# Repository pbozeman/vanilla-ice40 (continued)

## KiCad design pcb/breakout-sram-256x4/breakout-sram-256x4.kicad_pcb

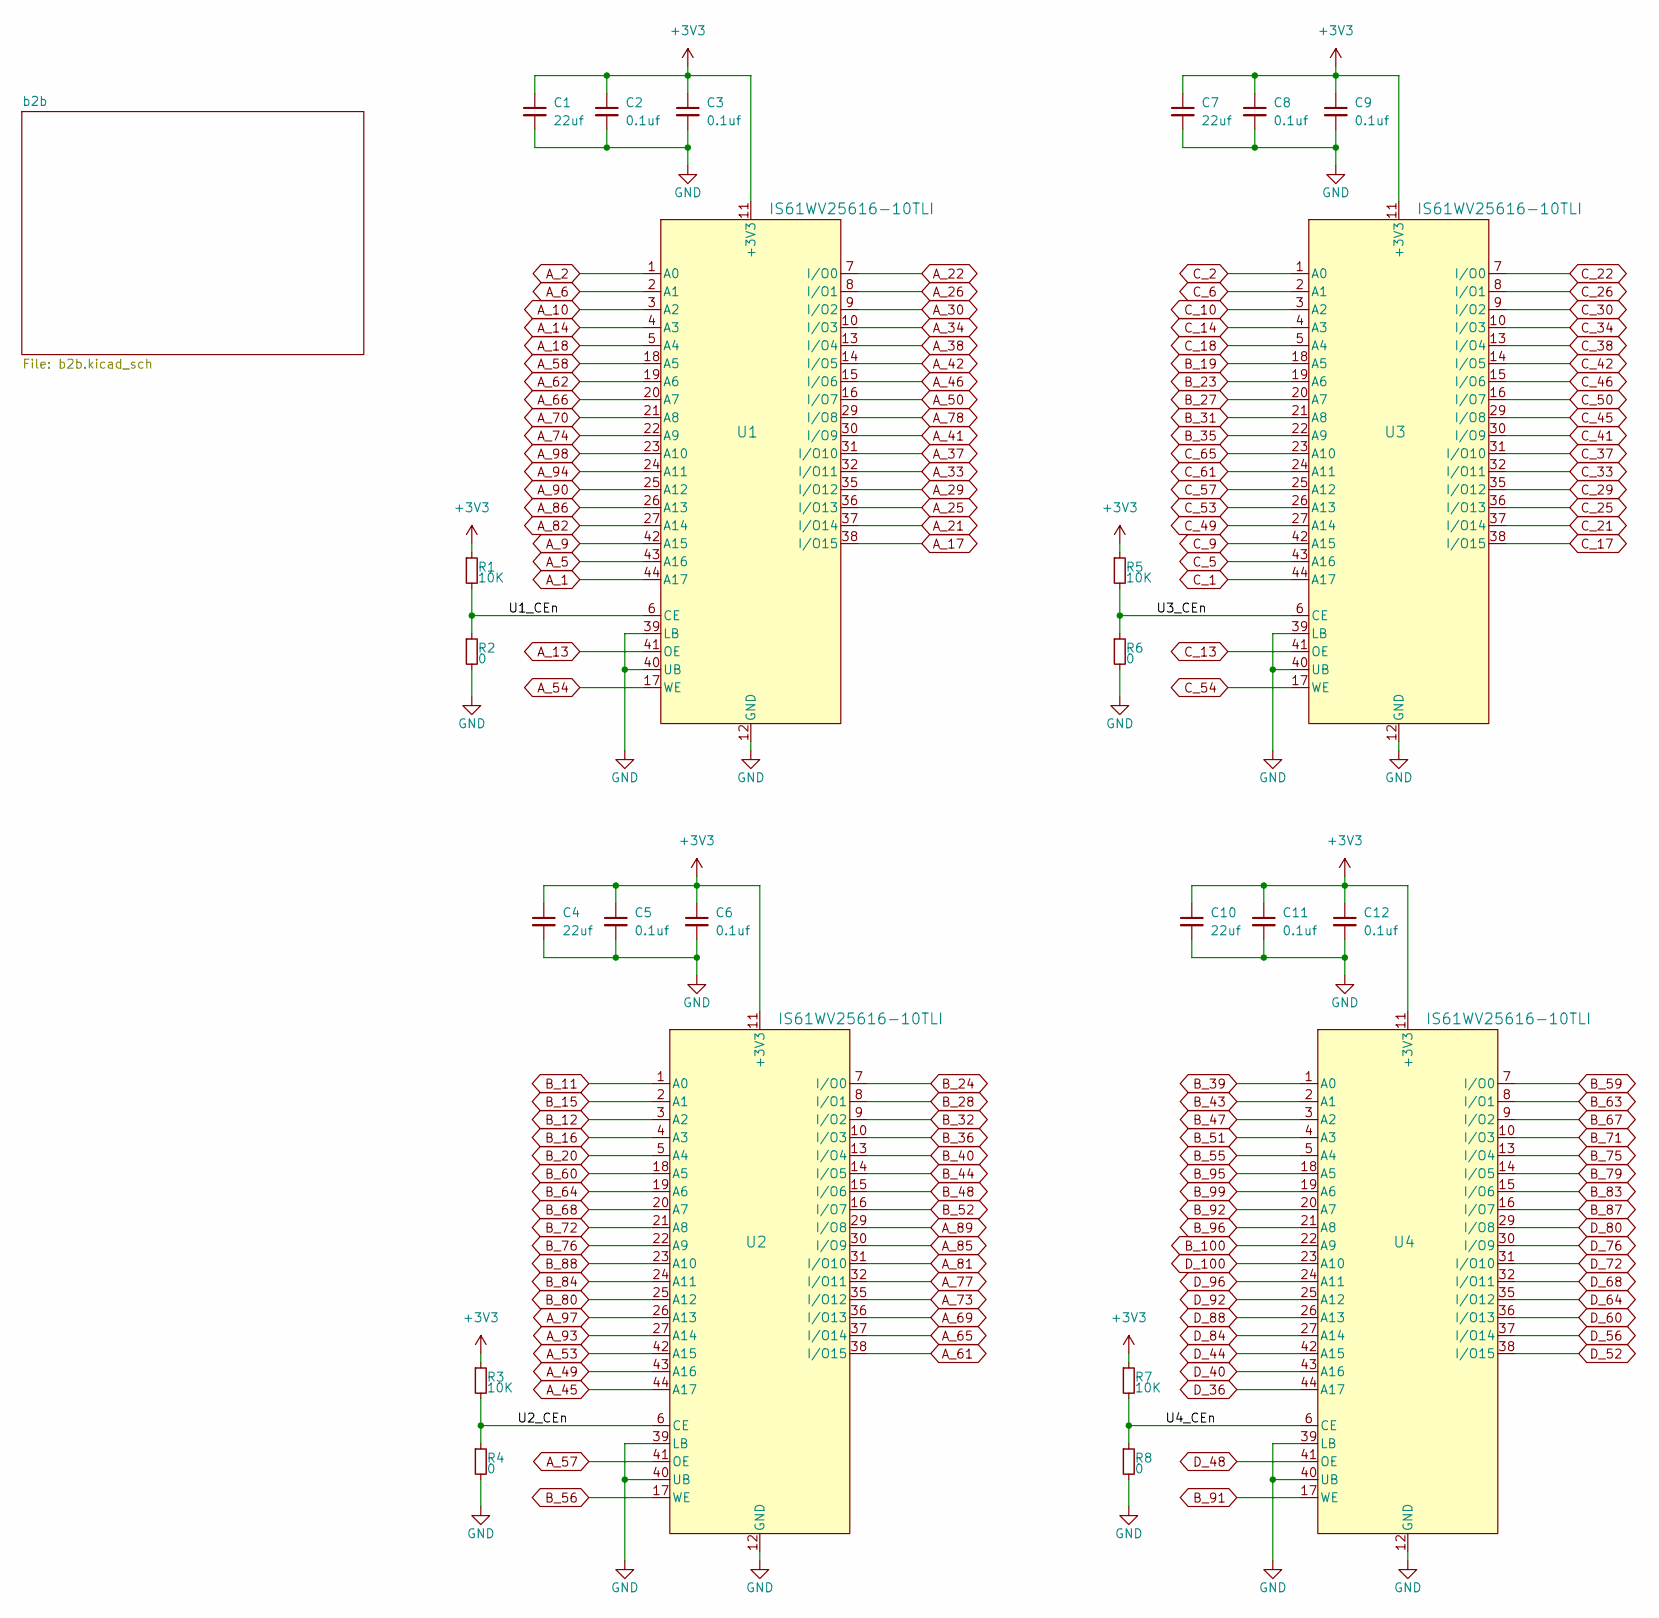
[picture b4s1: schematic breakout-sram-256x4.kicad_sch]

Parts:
C1, C4, C7, C10: 22uf; C_0603_1608Metric; LCSC Part # C59461
C2, C3, C5, C6, C8, C9, C11, C12: 0.1uf; C_0402_1005Metric; LCSC Part # C1525
R1, R3, R5, R7: 10K; R_0603_1608Metric; LCSC Part # C25804
R2, R4, R6, R8: 0; R_0603_1608Metric; LCSC Part # C21189
U1, U2, U3, U4: IS61WV25616-10TLI; 44L_TSOP-2_400_ISI; LCSC Part # C883296

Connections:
+3V3: C1.1, C2.1, C3.1, C4.1, C5.1, C6.1, C7.1, C8.1, C9.1, C10.1, C11.1, C12.1, R1.1, R3.1, R5.1, R7.1, U1.11 (+3V3), U1.33 (+3V3), U2.11 (+3V3), U2.33 (+3V3), U3.11 (+3V3), U3.33 (+3V3), U4.11 (+3V3), U4.33 (+3V3); also elsewhere on the board
/U1_CEn: R1.2, R2.1, U1.6 (CE)
/U2_CEn: R3.2, R4.1, U2.6 (CE)
/U3_CEn: R5.2, R6.1, U3.6 (CE)
/U4_CEn: R7.2, R8.1, U4.6 (CE)
A_1: U1.44 (A17); also elsewhere on the board
A_2: U1.1 (A0); also elsewhere on the board
A_5: U1.43 (A16); also elsewhere on the board
A_6: U1.2 (A1); also elsewhere on the board
A_9: U1.42 (A15); also elsewhere on the board
A_10: U1.3 (A2); also elsewhere on the board
A_13: U1.41 (OE); also elsewhere on the board
A_14: U1.4 (A3); also elsewhere on the board
A_17: U1.38 (I/O15); also elsewhere on the board
A_18: U1.5 (A4); also elsewhere on the board
A_21: U1.37 (I/O14); also elsewhere on the board
A_22: U1.7 (I/O0); also elsewhere on the board
A_25: U1.36 (I/O13); also elsewhere on the board
A_26: U1.8 (I/O1); also elsewhere on the board
A_29: U1.35 (I/O12); also elsewhere on the board
A_30: U1.9 (I/O2); also elsewhere on the board
A_33: U1.32 (I/O11); also elsewhere on the board
A_34: U1.10 (I/O3); also elsewhere on the board
A_37: U1.31 (I/O10); also elsewhere on the board
A_38: U1.13 (I/O4); also elsewhere on the board
A_41: U1.30 (I/O9); also elsewhere on the board
A_42: U1.14 (I/O5); also elsewhere on the board
A_45: U2.44 (A17); also elsewhere on the board
A_46: U1.15 (I/O6); also elsewhere on the board
A_49: U2.43 (A16); also elsewhere on the board
A_50: U1.16 (I/O7); also elsewhere on the board
A_53: U2.42 (A15); also elsewhere on the board
A_54: U1.17 (WE); also elsewhere on the board
A_57: U2.41 (OE); also elsewhere on the board
A_58: U1.18 (A5); also elsewhere on the board
A_61: U2.38 (I/O15); also elsewhere on the board
A_62: U1.19 (A6); also elsewhere on the board
A_65: U2.37 (I/O14); also elsewhere on the board
A_66: U1.20 (A7); also elsewhere on the board
A_69: U2.36 (I/O13); also elsewhere on the board
A_70: U1.21 (A8); also elsewhere on the board
A_73: U2.35 (I/O12); also elsewhere on the board
A_74: U1.22 (A9); also elsewhere on the board
A_77: U2.32 (I/O11); also elsewhere on the board
A_78: U1.29 (I/O8); also elsewhere on the board
A_81: U2.31 (I/O10); also elsewhere on the board
A_82: U1.27 (A14); also elsewhere on the board
A_85: U2.30 (I/O9); also elsewhere on the board
A_86: U1.26 (A13); also elsewhere on the board
A_89: U2.29 (I/O8); also elsewhere on the board
A_90: U1.25 (A12); also elsewhere on the board
A_93: U2.27 (A14); also elsewhere on the board
A_94: U1.24 (A11); also elsewhere on the board
A_97: U2.26 (A13); also elsewhere on the board
A_98: U1.23 (A10); also elsewhere on the board
B_11: U2.1 (A0); also elsewhere on the board
B_12: U2.3 (A2); also elsewhere on the board
B_15: U2.2 (A1); also elsewhere on the board
B_16: U2.4 (A3); also elsewhere on the board
B_19: U3.18 (A5); also elsewhere on the board
B_20: U2.5 (A4); also elsewhere on the board
B_23: U3.19 (A6); also elsewhere on the board
B_24: U2.7 (I/O0); also elsewhere on the board
B_27: U3.20 (A7); also elsewhere on the board
B_28: U2.8 (I/O1); also elsewhere on the board
B_31: U3.21 (A8); also elsewhere on the board
B_32: U2.9 (I/O2); also elsewhere on the board
B_35: U3.22 (A9); also elsewhere on the board
B_36: U2.10 (I/O3); also elsewhere on the board
B_39: U4.1 (A0); also elsewhere on the board
B_40: U2.13 (I/O4); also elsewhere on the board
B_43: U4.2 (A1); also elsewhere on the board
B_44: U2.14 (I/O5); also elsewhere on the board
B_47: U4.3 (A2); also elsewhere on the board
B_48: U2.15 (I/O6); also elsewhere on the board
B_51: U4.4 (A3); also elsewhere on the board
B_52: U2.16 (I/O7); also elsewhere on the board
B_55: U4.5 (A4); also elsewhere on the board
B_56: U2.17 (WE); also elsewhere on the board
B_59: U4.7 (I/O0); also elsewhere on the board
B_60: U2.18 (A5); also elsewhere on the board
B_63: U4.8 (I/O1); also elsewhere on the board
B_64: U2.19 (A6); also elsewhere on the board
B_67: U4.9 (I/O2); also elsewhere on the board
B_68: U2.20 (A7); also elsewhere on the board
B_71: U4.10 (I/O3); also elsewhere on the board
B_72: U2.21 (A8); also elsewhere on the board
B_75: U4.13 (I/O4); also elsewhere on the board
B_76: U2.22 (A9); also elsewhere on the board
B_79: U4.14 (I/O5); also elsewhere on the board
B_80: U2.25 (A12); also elsewhere on the board
B_83: U4.15 (I/O6); also elsewhere on the board
B_84: U2.24 (A11); also elsewhere on the board
B_87: U4.16 (I/O7); also elsewhere on the board
B_88: U2.23 (A10); also elsewhere on the board
B_91: U4.17 (WE); also elsewhere on the board
B_92: U4.20 (A7); also elsewhere on the board
B_95: U4.18 (A5); also elsewhere on the board
B_96: U4.21 (A8); also elsewhere on the board
B_99: U4.19 (A6); also elsewhere on the board
B_100: U4.22 (A9); also elsewhere on the board
C_1: U3.44 (A17); also elsewhere on the board
C_2: U3.1 (A0); also elsewhere on the board
C_5: U3.43 (A16); also elsewhere on the board
C_6: U3.2 (A1); also elsewhere on the board
C_9: U3.42 (A15); also elsewhere on the board
C_10: U3.3 (A2); also elsewhere on the board
C_13: U3.41 (OE); also elsewhere on the board
C_14: U3.4 (A3); also elsewhere on the board
C_17: U3.38 (I/O15); also elsewhere on the board
C_18: U3.5 (A4); also elsewhere on the board
C_21: U3.37 (I/O14); also elsewhere on the board
C_22: U3.7 (I/O0); also elsewhere on the board
C_25: U3.36 (I/O13); also elsewhere on the board
C_26: U3.8 (I/O1); also elsewhere on the board
C_29: U3.35 (I/O12); also elsewhere on the board
C_30: U3.9 (I/O2); also elsewhere on the board
C_33: U3.32 (I/O11); also elsewhere on the board
C_34: U3.10 (I/O3); also elsewhere on the board
C_37: U3.31 (I/O10); also elsewhere on the board
C_38: U3.13 (I/O4); also elsewhere on the board
C_41: U3.30 (I/O9); also elsewhere on the board
C_42: U3.14 (I/O5); also elsewhere on the board
C_45: U3.29 (I/O8); also elsewhere on the board
C_46: U3.15 (I/O6); also elsewhere on the board
C_49: U3.27 (A14); also elsewhere on the board
C_50: U3.16 (I/O7); also elsewhere on the board
C_53: U3.26 (A13); also elsewhere on the board
C_54: U3.17 (WE); also elsewhere on the board
C_57: U3.25 (A12); also elsewhere on the board
C_61: U3.24 (A11); also elsewhere on the board
C_65: U3.23 (A10); also elsewhere on the board
D_36: U4.44 (A17); also elsewhere on the board
D_40: U4.43 (A16); also elsewhere on the board
D_44: U4.42 (A15); also elsewhere on the board
D_48: U4.41 (OE); also elsewhere on the board
D_52: U4.38 (I/O15); also elsewhere on the board
D_56: U4.37 (I/O14); also elsewhere on the board
D_60: U4.36 (I/O13); also elsewhere on the board
D_64: U4.35 (I/O12); also elsewhere on the board
D_68: U4.32 (I/O11); also elsewhere on the board
D_72: U4.31 (I/O10); also elsewhere on the board
D_76: U4.30 (I/O9); also elsewhere on the board
D_80: U4.29 (I/O8); also elsewhere on the board
D_84: U4.27 (A14); also elsewhere on the board
D_88: U4.26 (A13); also elsewhere on the board
D_92: U4.25 (A12); also elsewhere on the board
D_96: U4.24 (A11); also elsewhere on the board
D_100: U4.23 (A10); also elsewhere on the board
GND: C1.2, C2.2, C3.2, C4.2, C5.2, C6.2, C7.2, C8.2, C9.2, C10.2, C11.2, C12.2, R2.2, R4.2, R6.2, R8.2, U1.12 (GND), U1.34 (GND), U1.39 (LB), U1.40 (UB), U2.12 (GND), U2.34 (GND), U2.39 (LB), U2.40 (UB), U3.12 (GND), U3.34 (GND), U3.39 (LB), U3.40 (UB), U4.12 (GND), U4.34 (GND), U4.39 (LB), U4.40 (UB); also elsewhere on the board

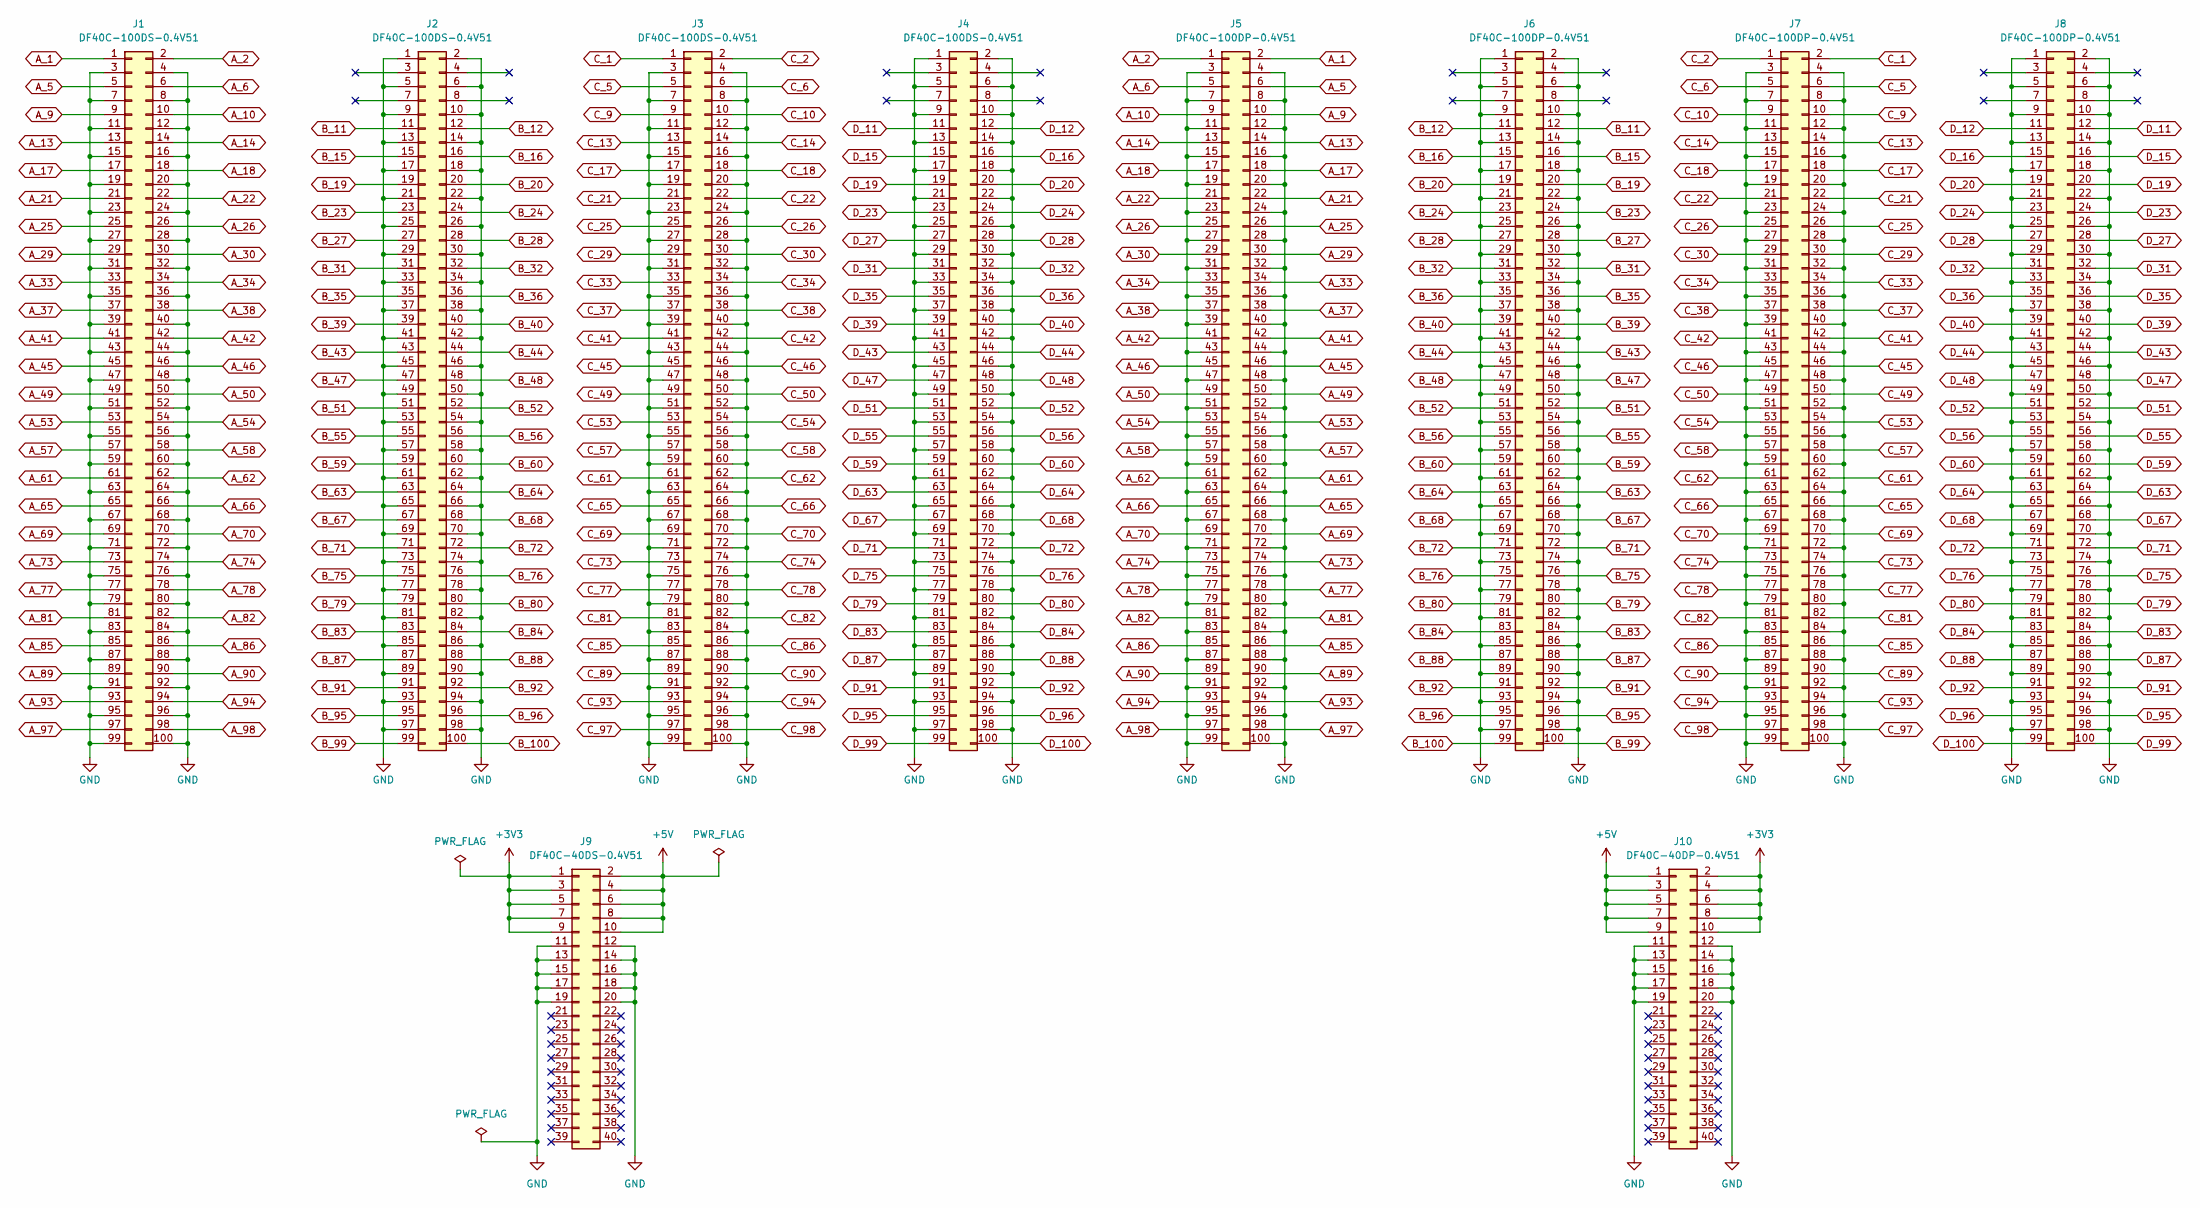
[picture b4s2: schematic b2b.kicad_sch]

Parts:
J1, J2, J3, J4: DF40C-100DS-0.4V51; DF40C100DS04V51; Digi-Key Part Number H11615CT-ND
J5, J6, J7, J8: DF40C-100DP-0.4V51; DF40C100DP04V51; Digi-Key Part Number H11614CT-ND
J9: DF40C-40DS-0.4V51; DF40C40DS04V51; Digi-Key Part Number H11625CT-ND
J10: DF40C-40DP-0.4V51; DF40C40DP04V51; Digi-Key Part Number H11624CT-ND

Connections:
+3V3: J9.1, J9.3, J9.5, J9.7, J9.9, J10.2, J10.4, J10.6, J10.8, J10.10; also elsewhere on the board
+5V: J9.2, J9.4, J9.6, J9.8, J9.10, J10.1, J10.3, J10.5, J10.7, J10.9
A_1: J1.1, J5.2; also elsewhere on the board
A_2: J1.2, J5.1; also elsewhere on the board
A_5: J1.5, J5.6; also elsewhere on the board
A_6: J1.6, J5.5; also elsewhere on the board
A_9: J1.9, J5.10; also elsewhere on the board
A_10: J1.10, J5.9; also elsewhere on the board
A_13: J1.13, J5.14; also elsewhere on the board
A_14: J1.14, J5.13; also elsewhere on the board
A_17: J1.17, J5.18; also elsewhere on the board
A_18: J1.18, J5.17; also elsewhere on the board
A_21: J1.21, J5.22; also elsewhere on the board
A_22: J1.22, J5.21; also elsewhere on the board
A_25: J1.25, J5.26; also elsewhere on the board
A_26: J1.26, J5.25; also elsewhere on the board
A_29: J1.29, J5.30; also elsewhere on the board
A_30: J1.30, J5.29; also elsewhere on the board
A_33: J1.33, J5.34; also elsewhere on the board
A_34: J1.34, J5.33; also elsewhere on the board
A_37: J1.37, J5.38; also elsewhere on the board
A_38: J1.38, J5.37; also elsewhere on the board
A_41: J1.41, J5.42; also elsewhere on the board
A_42: J1.42, J5.41; also elsewhere on the board
A_45: J1.45, J5.46; also elsewhere on the board
A_46: J1.46, J5.45; also elsewhere on the board
A_49: J1.49, J5.50; also elsewhere on the board
A_50: J1.50, J5.49; also elsewhere on the board
A_53: J1.53, J5.54; also elsewhere on the board
A_54: J1.54, J5.53; also elsewhere on the board
A_57: J1.57, J5.58; also elsewhere on the board
A_58: J1.58, J5.57; also elsewhere on the board
A_61: J1.61, J5.62; also elsewhere on the board
A_62: J1.62, J5.61; also elsewhere on the board
A_65: J1.65, J5.66; also elsewhere on the board
A_66: J1.66, J5.65; also elsewhere on the board
A_69: J1.69, J5.70; also elsewhere on the board
A_70: J1.70, J5.69; also elsewhere on the board
A_73: J1.73, J5.74; also elsewhere on the board
A_74: J1.74, J5.73; also elsewhere on the board
A_77: J1.77, J5.78; also elsewhere on the board
A_78: J1.78, J5.77; also elsewhere on the board
A_81: J1.81, J5.82; also elsewhere on the board
A_82: J1.82, J5.81; also elsewhere on the board
A_85: J1.85, J5.86; also elsewhere on the board
A_86: J1.86, J5.85; also elsewhere on the board
A_89: J1.89, J5.90; also elsewhere on the board
A_90: J1.90, J5.89; also elsewhere on the board
A_93: J1.93, J5.94; also elsewhere on the board
A_94: J1.94, J5.93; also elsewhere on the board
A_97: J1.97, J5.98; also elsewhere on the board
A_98: J1.98, J5.97; also elsewhere on the board
B_11: J2.11, J6.12; also elsewhere on the board
B_12: J2.12, J6.11; also elsewhere on the board
B_15: J2.15, J6.16; also elsewhere on the board
B_16: J2.16, J6.15; also elsewhere on the board
B_19: J2.19, J6.20; also elsewhere on the board
B_20: J2.20, J6.19; also elsewhere on the board
B_23: J2.23, J6.24; also elsewhere on the board
B_24: J2.24, J6.23; also elsewhere on the board
B_27: J2.27, J6.28; also elsewhere on the board
B_28: J2.28, J6.27; also elsewhere on the board
B_31: J2.31, J6.32; also elsewhere on the board
B_32: J2.32, J6.31; also elsewhere on the board
B_35: J2.35, J6.36; also elsewhere on the board
B_36: J2.36, J6.35; also elsewhere on the board
B_39: J2.39, J6.40; also elsewhere on the board
B_40: J2.40, J6.39; also elsewhere on the board
B_43: J2.43, J6.44; also elsewhere on the board
B_44: J2.44, J6.43; also elsewhere on the board
B_47: J2.47, J6.48; also elsewhere on the board
B_48: J2.48, J6.47; also elsewhere on the board
B_51: J2.51, J6.52; also elsewhere on the board
B_52: J2.52, J6.51; also elsewhere on the board
B_55: J2.55, J6.56; also elsewhere on the board
B_56: J2.56, J6.55; also elsewhere on the board
B_59: J2.59, J6.60; also elsewhere on the board
B_60: J2.60, J6.59; also elsewhere on the board
B_63: J2.63, J6.64; also elsewhere on the board
B_64: J2.64, J6.63; also elsewhere on the board
B_67: J2.67, J6.68; also elsewhere on the board
B_68: J2.68, J6.67; also elsewhere on the board
B_71: J2.71, J6.72; also elsewhere on the board
B_72: J2.72, J6.71; also elsewhere on the board
B_75: J2.75, J6.76; also elsewhere on the board
B_76: J2.76, J6.75; also elsewhere on the board
B_79: J2.79, J6.80; also elsewhere on the board
B_80: J2.80, J6.79; also elsewhere on the board
B_83: J2.83, J6.84; also elsewhere on the board
B_84: J2.84, J6.83; also elsewhere on the board
B_87: J2.87, J6.88; also elsewhere on the board
B_88: J2.88, J6.87; also elsewhere on the board
B_91: J2.91, J6.92; also elsewhere on the board
B_92: J2.92, J6.91; also elsewhere on the board
B_95: J2.95, J6.96; also elsewhere on the board
B_96: J2.96, J6.95; also elsewhere on the board
B_99: J2.99, J6.100; also elsewhere on the board
B_100: J2.100, J6.99; also elsewhere on the board
C_1: J3.1, J7.2; also elsewhere on the board
C_2: J3.2, J7.1; also elsewhere on the board
C_5: J3.5, J7.6; also elsewhere on the board
C_6: J3.6, J7.5; also elsewhere on the board
C_9: J3.9, J7.10; also elsewhere on the board
C_10: J3.10, J7.9; also elsewhere on the board
C_13: J3.13, J7.14; also elsewhere on the board
C_14: J3.14, J7.13; also elsewhere on the board
C_17: J3.17, J7.18; also elsewhere on the board
C_18: J3.18, J7.17; also elsewhere on the board
C_21: J3.21, J7.22; also elsewhere on the board
C_22: J3.22, J7.21; also elsewhere on the board
C_25: J3.25, J7.26; also elsewhere on the board
C_26: J3.26, J7.25; also elsewhere on the board
C_29: J3.29, J7.30; also elsewhere on the board
C_30: J3.30, J7.29; also elsewhere on the board
C_33: J3.33, J7.34; also elsewhere on the board
C_34: J3.34, J7.33; also elsewhere on the board
C_37: J3.37, J7.38; also elsewhere on the board
C_38: J3.38, J7.37; also elsewhere on the board
C_41: J3.41, J7.42; also elsewhere on the board
C_42: J3.42, J7.41; also elsewhere on the board
C_45: J3.45, J7.46; also elsewhere on the board
C_46: J3.46, J7.45; also elsewhere on the board
C_49: J3.49, J7.50; also elsewhere on the board
C_50: J3.50, J7.49; also elsewhere on the board
C_53: J3.53, J7.54; also elsewhere on the board
C_54: J3.54, J7.53; also elsewhere on the board
C_57: J3.57, J7.58; also elsewhere on the board
C_58: J3.58, J7.57
C_61: J3.61, J7.62; also elsewhere on the board
C_62: J3.62, J7.61
C_65: J3.65, J7.66; also elsewhere on the board
C_66: J3.66, J7.65
C_69: J3.69, J7.70
C_70: J3.70, J7.69
C_73: J3.73, J7.74
C_74: J3.74, J7.73
C_77: J3.77, J7.78
C_78: J3.78, J7.77
C_81: J3.81, J7.82
C_82: J3.82, J7.81
C_85: J3.85, J7.86
C_86: J3.86, J7.85
C_89: J3.89, J7.90
C_90: J3.90, J7.89
C_93: J3.93, J7.94
C_94: J3.94, J7.93
C_97: J3.97, J7.98
C_98: J3.98, J7.97
D_11: J4.11, J8.12
D_12: J4.12, J8.11
D_15: J4.15, J8.16
D_16: J4.16, J8.15
D_19: J4.19, J8.20
D_20: J4.20, J8.19
D_23: J4.23, J8.24
D_24: J4.24, J8.23
D_27: J4.27, J8.28
D_28: J4.28, J8.27
D_31: J4.31, J8.32
D_32: J4.32, J8.31
D_35: J4.35, J8.36
D_36: J4.36, J8.35; also elsewhere on the board
D_39: J4.39, J8.40
D_40: J4.40, J8.39; also elsewhere on the board
D_43: J4.43, J8.44
D_44: J4.44, J8.43; also elsewhere on the board
D_47: J4.47, J8.48
D_48: J4.48, J8.47; also elsewhere on the board
D_51: J4.51, J8.52
D_52: J4.52, J8.51; also elsewhere on the board
D_55: J4.55, J8.56
D_56: J4.56, J8.55; also elsewhere on the board
D_59: J4.59, J8.60
D_60: J4.60, J8.59; also elsewhere on the board
D_63: J4.63, J8.64
D_64: J4.64, J8.63; also elsewhere on the board
D_67: J4.67, J8.68
D_68: J4.68, J8.67; also elsewhere on the board
D_71: J4.71, J8.72
D_72: J4.72, J8.71; also elsewhere on the board
D_75: J4.75, J8.76
D_76: J4.76, J8.75; also elsewhere on the board
D_79: J4.79, J8.80
D_80: J4.80, J8.79; also elsewhere on the board
D_83: J4.83, J8.84
D_84: J4.84, J8.83; also elsewhere on the board
D_87: J4.87, J8.88
D_88: J4.88, J8.87; also elsewhere on the board
D_91: J4.91, J8.92
D_92: J4.92, J8.91; also elsewhere on the board
D_95: J4.95, J8.96
D_96: J4.96, J8.95; also elsewhere on the board
D_99: J4.99, J8.100
D_100: J4.100, J8.99; also elsewhere on the board
GND: J1.3, J1.4, J1.7, J1.8, J1.11, J1.12, J1.15, J1.16, J1.19, J1.20, J1.23, J1.24, J1.27, J1.28, J1.31, J1.32, J1.35, J1.36, J1.39, J1.40, J1.43, J1.44, J1.47, J1.48, J1.51, J1.52, J1.55, J1.56, J1.59, J1.60, J1.63, J1.64, J1.67, J1.68, J1.71, J1.72, J1.75, J1.76, J1.79, J1.80, J1.83, J1.84, J1.87, J1.88, J1.91, J1.92, J1.95, J1.96, J1.99, J1.100, J2.1, J2.2, J2.5, J2.6, J2.9, J2.10, J2.13, J2.14, J2.17, J2.18, J2.21, J2.22, J2.25, J2.26, J2.29, J2.30, J2.33, J2.34, J2.37, J2.38, J2.41, J2.42, J2.45, J2.46, J2.49, J2.50, J2.53, J2.54, J2.57, J2.58, J2.61, J2.62, J2.65, J2.66, J2.69, J2.70, J2.73, J2.74, J2.77, J2.78, J2.81, J2.82, J2.85, J2.86, J2.89, J2.90, J2.93, J2.94, J2.97, J2.98, J3.3, J3.4, J3.7, J3.8, J3.11, J3.12, J3.15, J3.16, J3.19, J3.20, J3.23, J3.24, J3.27, J3.28, J3.31, J3.32, J3.35, J3.36, J3.39, J3.40, J3.43, J3.44, J3.47, J3.48, J3.51, J3.52, J3.55, J3.56, J3.59, J3.60, J3.63, J3.64, J3.67, J3.68, J3.71, J3.72, J3.75, J3.76, J3.79, J3.80, J3.83, J3.84, J3.87, J3.88, J3.91, J3.92, J3.95, J3.96, J3.99, J3.100, J4.1, J4.2, J4.5, J4.6, J4.9, J4.10, J4.13, J4.14, J4.17, J4.18, J4.21, J4.22, J4.25, J4.26, J4.29, J4.30, J4.33, J4.34, J4.37, J4.38, J4.41, J4.42, J4.45, J4.46, J4.49, J4.50, J4.53, J4.54, J4.57, J4.58, J4.61, J4.62, J4.65, J4.66, J4.69, J4.70, J4.73, J4.74, J4.77, J4.78, J4.81, J4.82, J4.85, J4.86, J4.89, J4.90, J4.93, J4.94, J4.97, J4.98, J5.3, J5.4, J5.7, J5.8, J5.11, J5.12, J5.15, J5.16, J5.19, J5.20, J5.23, J5.24, J5.27, J5.28, J5.31, J5.32, J5.35, J5.36, J5.39, J5.40, J5.43, J5.44, J5.47, J5.48, J5.51, J5.52, J5.55, J5.56, J5.59, J5.60, J5.63, J5.64, J5.67, J5.68, J5.71, J5.72, J5.75, J5.76, J5.79, J5.80, J5.83, J5.84, J5.87, J5.88, J5.91, J5.92, J5.95, J5.96, J5.99, J5.100, J6.1, J6.2, J6.5, J6.6, J6.9, J6.10, J6.13, J6.14, J6.17, J6.18, J6.21, J6.22, J6.25, J6.26, J6.29, J6.30, J6.33, J6.34, J6.37, J6.38, J6.41, J6.42, J6.45, J6.46, J6.49, J6.50, J6.53, J6.54, J6.57, J6.58, J6.61, J6.62, J6.65, J6.66, J6.69, J6.70, J6.73, J6.74, J6.77, J6.78, J6.81, J6.82, J6.85, J6.86, J6.89, J6.90, J6.93, J6.94, J6.97, J6.98, J7.3, J7.4, J7.7, J7.8, J7.11, J7.12, J7.15, J7.16, J7.19, J7.20, J7.23, J7.24, J7.27, J7.28, J7.31, J7.32, J7.35, J7.36, J7.39, J7.40, J7.43, J7.44, J7.47, J7.48, J7.51, J7.52, J7.55, J7.56, J7.59, J7.60, J7.63, J7.64, J7.67, J7.68, J7.71, J7.72, J7.75, J7.76, J7.79, J7.80, J7.83, J7.84, J7.87, J7.88, J7.91, J7.92, J7.95, J7.96, J7.99, J7.100, J8.1, J8.2, J8.5, J8.6, J8.9, J8.10, J8.13, J8.14, J8.17, J8.18, J8.21, J8.22, J8.25, J8.26, J8.29, J8.30, J8.33, J8.34, J8.37, J8.38, J8.41, J8.42, J8.45, J8.46, J8.49, J8.50, J8.53, J8.54, J8.57, J8.58, J8.61, J8.62, J8.65, J8.66, J8.69, J8.70, J8.73, J8.74, J8.77, J8.78, J8.81, J8.82, J8.85, J8.86, J8.89, J8.90, J8.93, J8.94, J8.97, J8.98, J9.11, J9.12, J9.13, J9.14, J9.15, J9.16, J9.17, J9.18, J9.19, J9.20, J10.11, J10.12, J10.13, J10.14, J10.15, J10.16, J10.17, J10.18, J10.19, J10.20; also elsewhere on the board

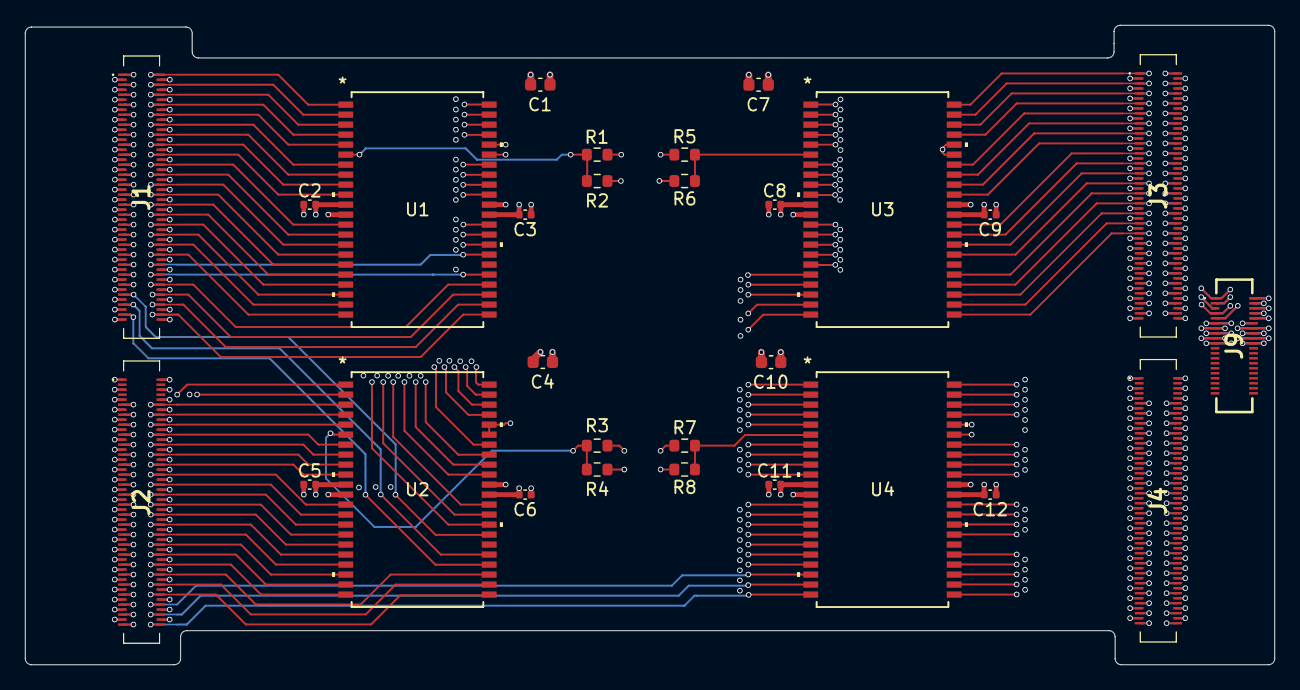
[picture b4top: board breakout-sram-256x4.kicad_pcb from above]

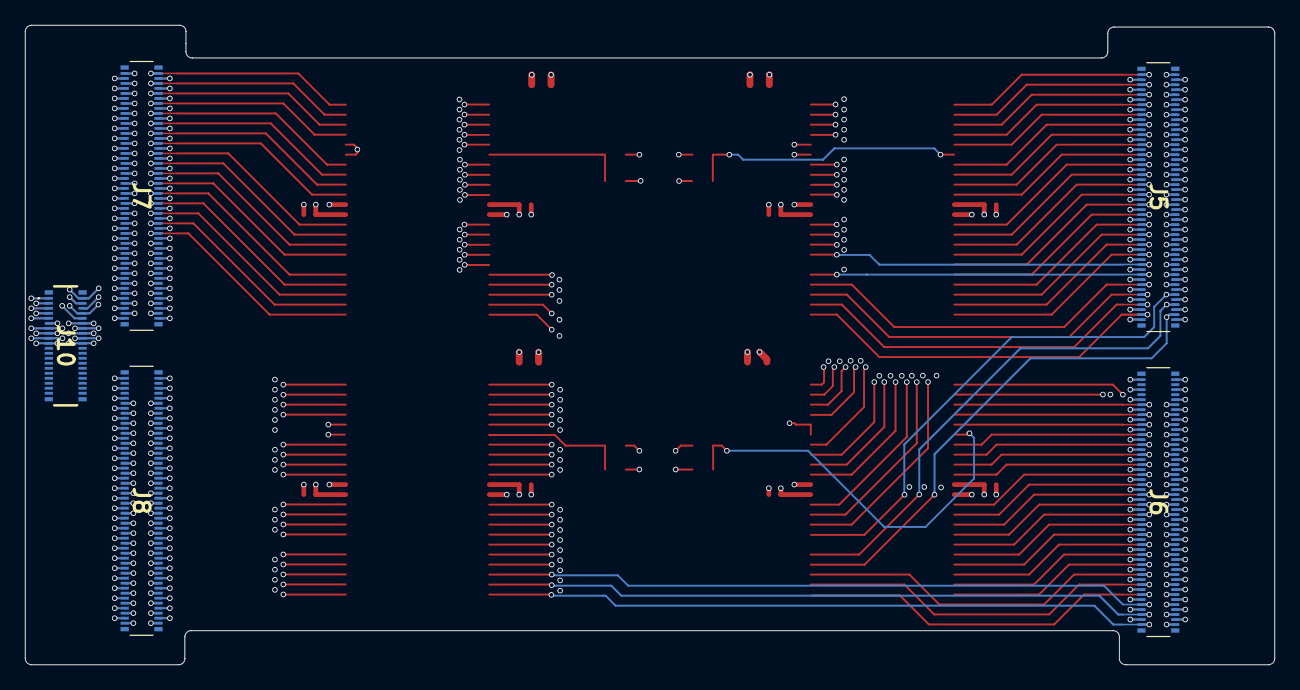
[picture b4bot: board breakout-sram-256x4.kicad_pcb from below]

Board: 8 copper layers, 100.0 x 51.2 mm, 34 parts (5 on the bottom side), 199 nets.

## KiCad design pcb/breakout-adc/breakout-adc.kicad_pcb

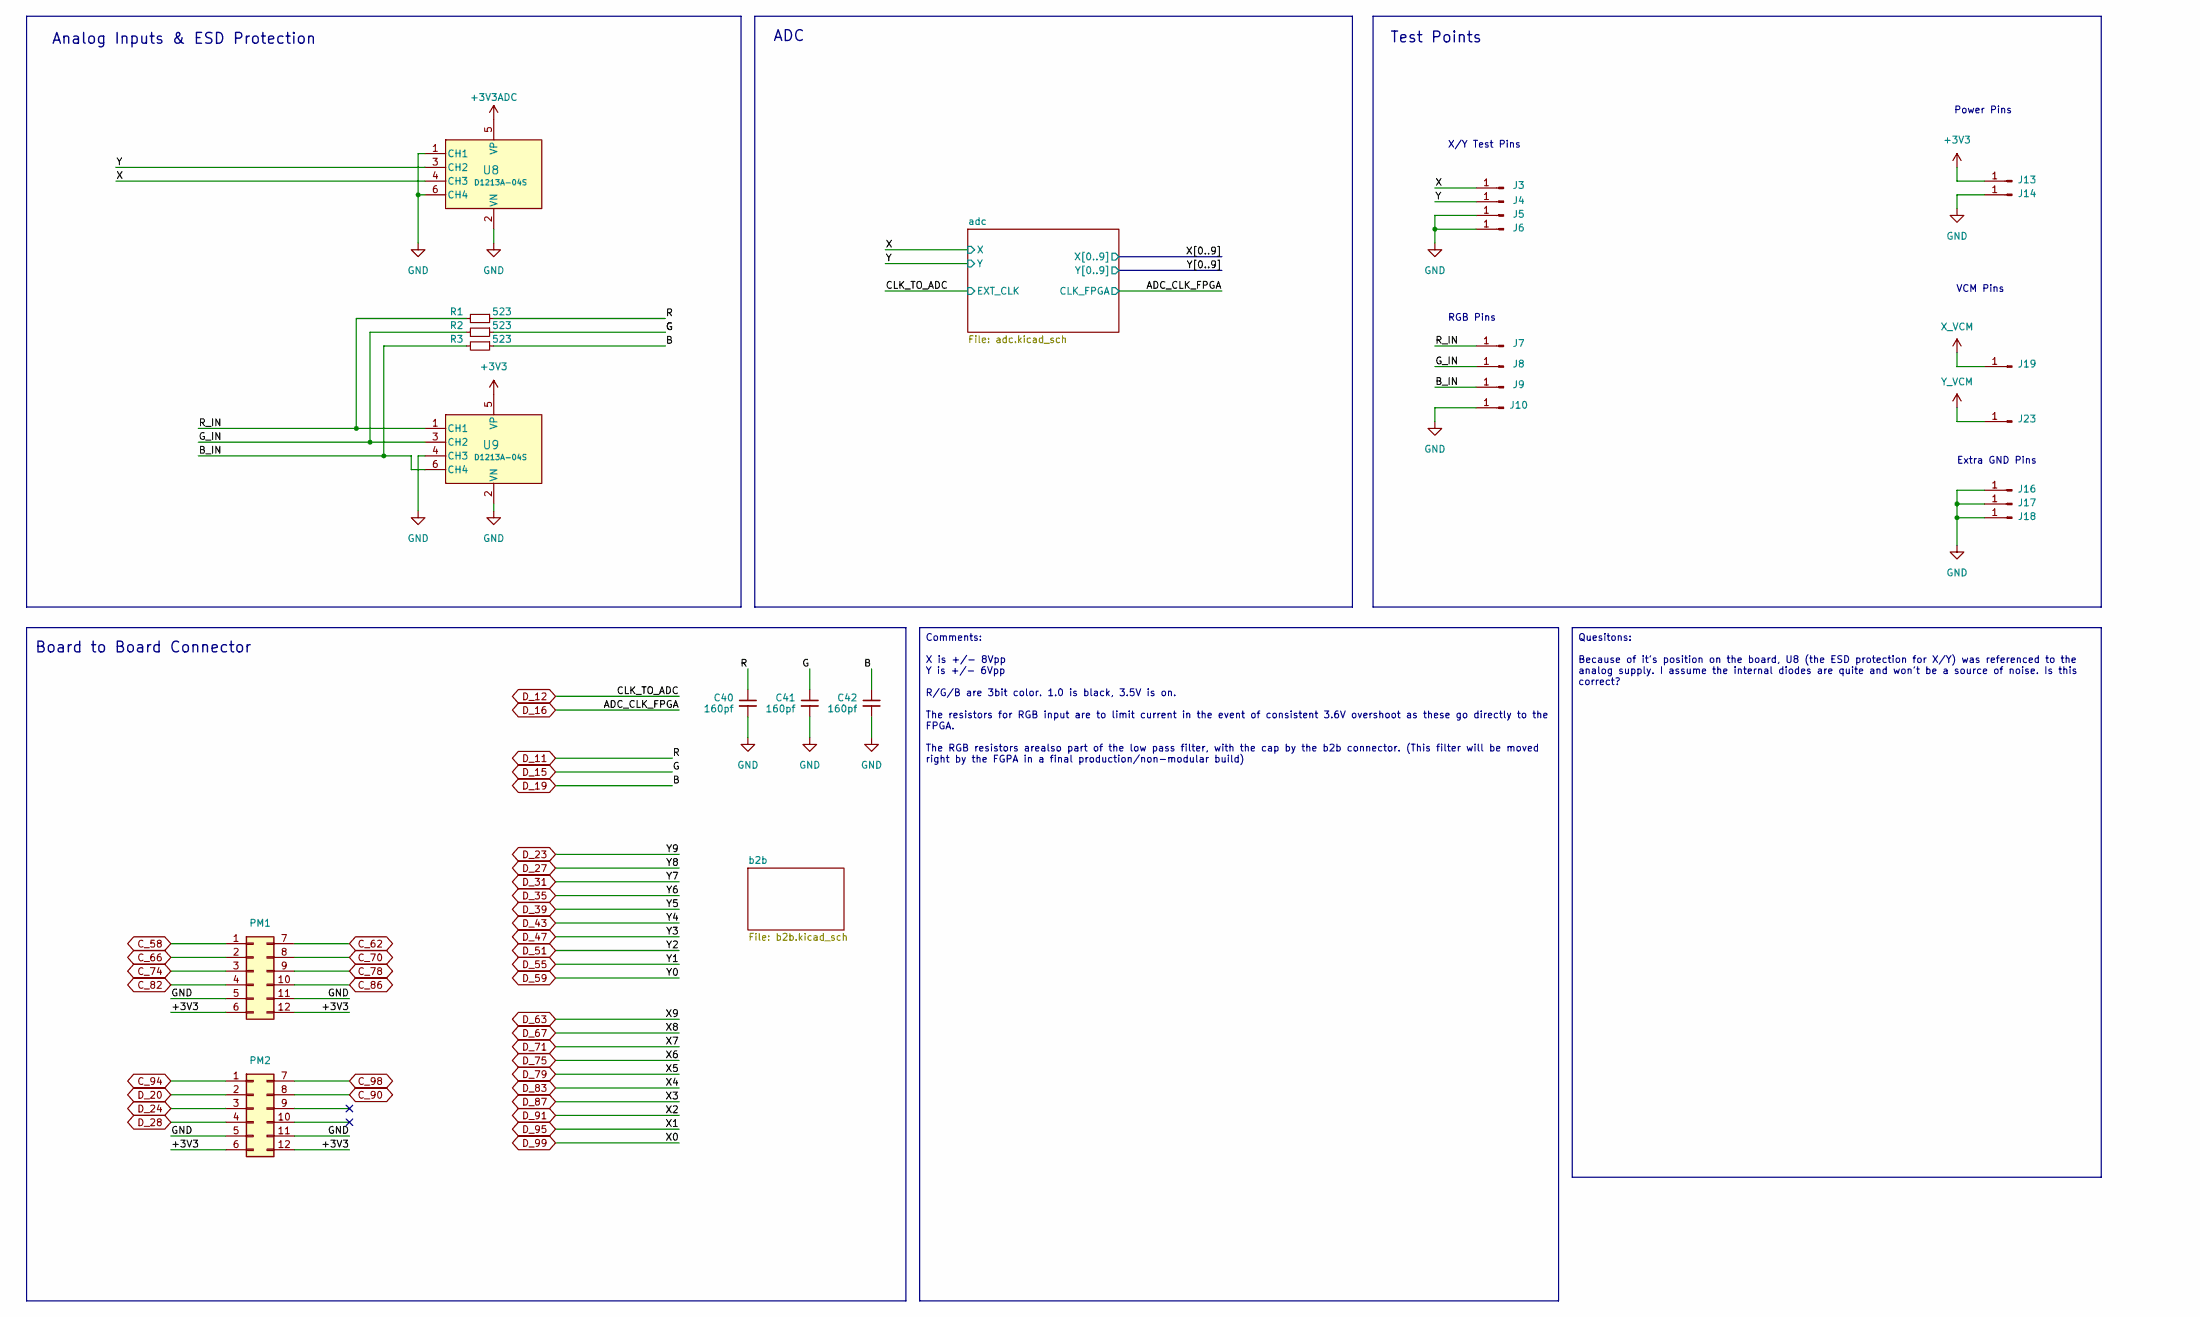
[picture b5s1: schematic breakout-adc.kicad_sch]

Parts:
C40, C41, C42: 160pf; C_0402_1005Metric; Digi-Key Part Number 490-GRT1555C1H161FA02DCT-ND
J3, J4: White; KEYSTONE_5002; Digi-Key Part Number 36-5002-ND
J5, J6, J10, J14, J16, J17, J18: Black; KEYSTONE_5001; Digi-Key Part Number 36-5001-ND
J7, J13: Red; KEYSTONE_5000; Digi-Key Part Number 36-5000-ND
J8: Green; KEYSTONE_5116; Digi-Key Part Number 36-5116-ND
J9, J19, J23: Blue; KEYSTONE_5117; Digi-Key Part Number 36-5117-ND
PM1, PM2: Conn_02x06_Top_Bottom; PMOD_12p_Horizontal; Digi-Key Part Number S5559-ND
R1, R2, R3: 523; R_0805_2012Metric; LCSC Part # C227952
U8, U9: D1213A-04S; SOT-363_DIO; Digi-Key Part Number D1213A-04S-7DICT-ND

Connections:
+3V3: J13.1, PM1.6, PM1.12, PM2.6, PM2.12, U9.5 (VP); also elsewhere on the board
+3V3ADC: U8.5 (VP); also elsewhere on the board
/B_IN: J9.1, R3.2, U9.6 (CH4)
/G_IN: J8.1, R2.2, U9.3 (CH2)
/R_IN: J7.1, R1.2, U9.1 (CH1)
/X: J3.1, U8.4 (CH3); also elsewhere on the board
/Y: J4.1, U8.3 (CH2); also elsewhere on the board
C_58: PM1.1; also elsewhere on the board
C_62: PM1.7; also elsewhere on the board
C_66: PM1.2; also elsewhere on the board
C_70: PM1.8; also elsewhere on the board
C_74: PM1.3; also elsewhere on the board
C_78: PM1.9; also elsewhere on the board
C_82: PM1.4; also elsewhere on the board
C_86: PM1.10; also elsewhere on the board
C_90: PM2.8; also elsewhere on the board
C_94: PM2.1; also elsewhere on the board
C_98: PM2.7; also elsewhere on the board
D_11: C40.1, R1.1; also elsewhere on the board
D_15: C41.1, R2.1; also elsewhere on the board
D_19: C42.1, R3.1; also elsewhere on the board
D_20: PM2.2; also elsewhere on the board
D_24: PM2.3; also elsewhere on the board
D_28: PM2.4; also elsewhere on the board
GND: C40.2, C41.2, C42.2, J5.1, J6.1, J10.1, J14.1, J16.1, J17.1, J18.1, PM1.5, PM1.11, PM2.5, PM2.11, U8.1 (CH1), U8.2 (VN), U8.6 (CH4), U9.2 (VN), U9.4 (CH3); also elsewhere on the board
X_VCM: J19.1; also elsewhere on the board
Y_VCM: J23.1; also elsewhere on the board

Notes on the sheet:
Comments: X is +/- 8Vpp Y is +/- 6Vpp R/G/B are 3bit color. 1.0 is black, 3.5V is on. The resistors for RGB input are to limit current in the event of consistent 3.6V overshoot as these go directly to the FPGA. The RGB resistors arealso part of the low pass filter, with the cap by the b2b connector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
Quesitons: Because of it's position on the board, U8 (the ESD protection for X/Y) was referenced to the analog supply. I assume the internal diodes are quite and won't be a source of noise. Is this correct?
Power Pins
Test Points
VCM Pins
Extra GND Pins
Board to Board Connector
Analog Inputs & ESD Protection
X/Y Test Pins
RGB Pins
ADC
